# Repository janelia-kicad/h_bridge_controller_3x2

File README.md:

# h_bridge_controller_3x2

Authors:

    Peter Polidoro <polidorop@janelia.hhmi.org>

License:

    BSD

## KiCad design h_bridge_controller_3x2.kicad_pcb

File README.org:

#+TITLE: h_bridge_controller_3x2
#+AUTHOR: Peter Polidoro
#+EMAIL: peter@polidoro.io

* Repository Information
  - Author :: Peter Polidoro
  - License :: Open-Source Hardware

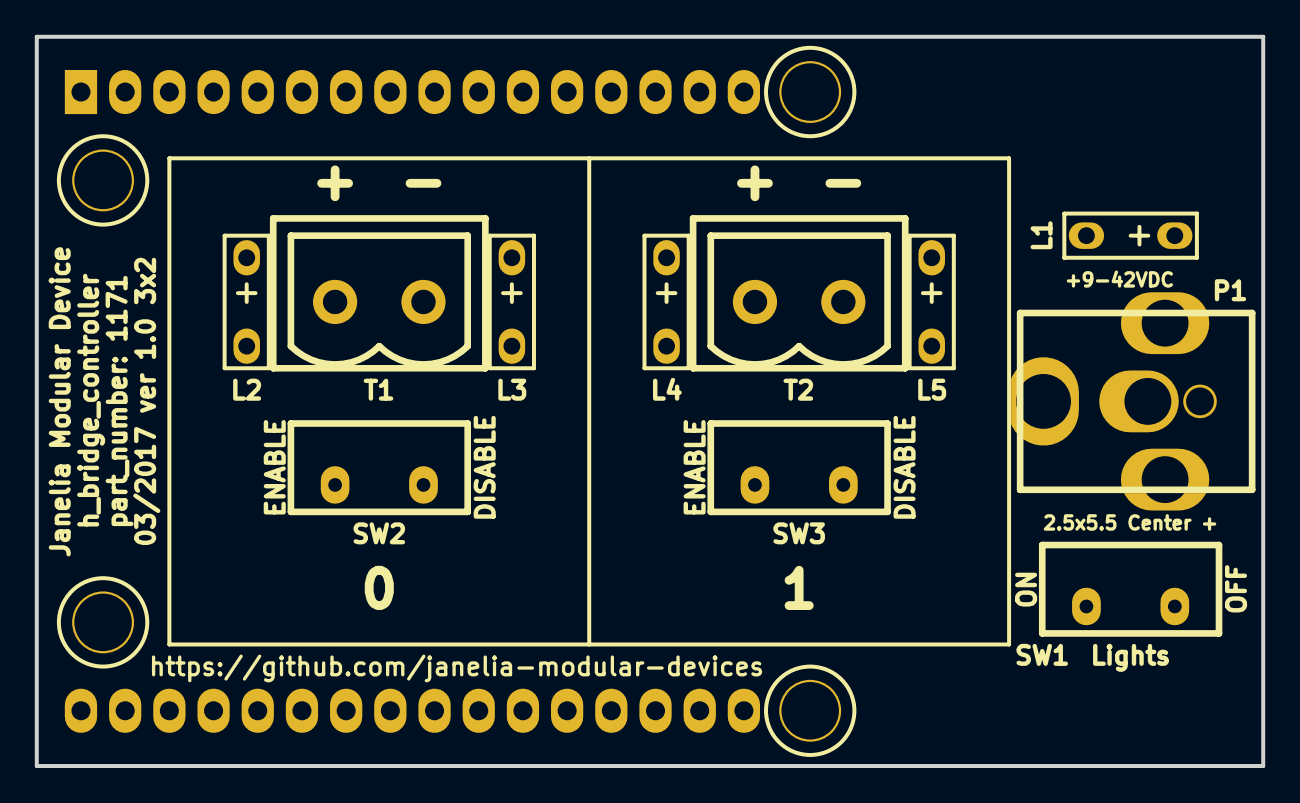
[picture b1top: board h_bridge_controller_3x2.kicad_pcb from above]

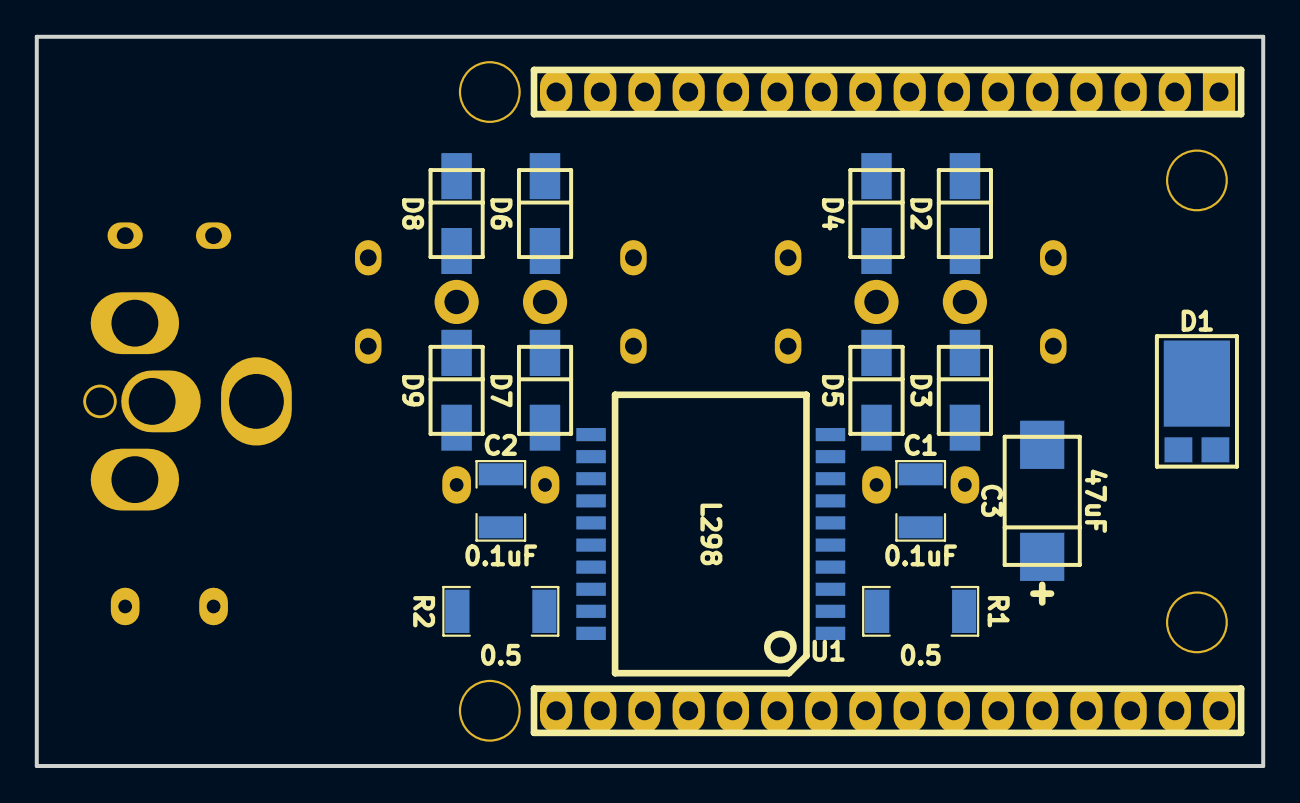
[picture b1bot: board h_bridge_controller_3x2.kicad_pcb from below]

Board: 2 copper layers, 70.5 x 41.9 mm, 27 parts (15 on the bottom side), 19 nets, no tracks yet.

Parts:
C1, C2: 0.1uF; SM1210
C3: 47uF; SM2917_POL
D1: diode_schottky_45V_10A; CFP15
D2, D3, D4, D5, D6, D7, D8, D9: diode_schottky_40V_1A; DO-214AC_SMA
L1, L2, L3, L4, L5: LED_24V; LED_555-3XXX
MDB1: MODULAR_DEVICE_BASE_3X2_MALE
P1: PWR_JACK_2.5x5.5; DCJACK_2PIN_HIGHCURRENT
R1, R2: 0.5; SM2010
SW1, SW2, SW3: SPST_SLIDE_AS
T1, T2: TERM_BLK_HDR_2POS_VERT_0.2IN
U1: L298; POWERSO20

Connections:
/DIR_A_0: MDB1.18, U1.7
/DIR_A_1: MDB1.20, U1.13
/DIR_B_0: MDB1.19, U1.9
/DIR_B_1: MDB1.21, U1.15
/ENABLE_0: MDB1.22, U1.8
/ENABLE_1: MDB1.23, U1.14
/SENSE_0: MDB1.14, R1.1, U1.2
/SENSE_1: MDB1.15, R2.1, U1.19
/USER_ENABLE_0: MDB1.5, SW2.1
/USER_ENABLE_1: MDB1.6, SW3.1
/h_bridge_0/OUT_+_0: D2.2, D3.1, L2.1, T1.1, U1.4
/h_bridge_0/OUT_+_1: D6.2, D7.1, L4.1, T2.1, U1.16
/h_bridge_0/OUT_-_0: D4.2, D5.1, L3.1, T1.2, U1.5
/h_bridge_0/OUT_-_1: D8.2, D9.1, L5.1, T2.2, U1.17
GND: C1.2, C2.2, C3.2, D3.2, D5.2, D7.2, D9.2, MDB1.GND, P1.2, R1.2, R2.2, SW1.1, SW2.3, SW3.3, U1.1, U1.10, U1.11, U1.20
LED_GND: L1.2, L2.2, L3.2, L4.2, L5.2, SW1.3
VAA: C1.1, C3.1, D1.2, D2.1, D4.1, D6.1, D8.1, L1.1, P1.1, U1.6
VDD: D1.1, MDB1.VDD
VEE: C2.1, MDB1.VEE, U1.12

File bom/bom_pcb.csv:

Item,Reference(s),Value,Quantity,Description,PartNumber,Vendor
1,C1 C2,0.1uF,2,CAP CER 0.1UF 50V 10% X7R 1210,399-13229-1-ND,digikey
2,C3,47uF,1,CAP TANT 47UF 35V 10% 2917,399-3821-1-ND,digikey
3,D1,diode_schottky_45V_10A,1,DIODE SCHOTTKY 45V 10A CFP15,568-11697-1-ND,digikey
4,D2 D3 D4 D5 D6 D7 D8 D9,diode_schottky_40V_1A,8,DIODE SCHOTTKY 40V 1A SMA,SS14CT-ND,digikey
5,L1 L2 L3 L4 L5,LED_24V,5,LED 2MM 24V VERTICAL RED PC MNT,350-1723-ND,digikey
6,MDB1,MODULAR_DEVICE_BASE_3X2_MALE,2,16 Position Header Through Hole Male Pins,S1011E-16-ND,digikey
7,P1,PWR_JACK_2.5x5.5,1,CONN PWR JACK DC 2.5X5.5 8A T/H,CP-063BH-ND,digikey
8,R1 R2,0.5,2,RES SMD 0.5 OHM 1% 1W 2010,CSRN2010FKR500CT-ND,digikey
9,SW1 SW2 SW3,SPST_SLIDE_AS,3,SWITCH SLIDE SPST 0.4VA 28V,360-2610-ND,digikey
10,T1 T2,TERM_BLK_HDR_2POS_VERT_0.2IN,2,TERM BLOCK HDR 2POS VERT 5.08MM,277-1150-ND,digikey
11,U1,L298,1,IC BRIDGE DRIVER PAR 20POWERSO,497-3624-1-ND,digikey

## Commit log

2017-01-24 Initial commit.
2017-03-07 Added template_3x2 files.
2017-03-07 Added components and footprints.
2017-03-07 Progress towards v1.0.
2017-03-08 Finished version 1.0.
2017-03-24 Updated documentation.
2017-06-15 Removed .cmp file.
2017-07-14 Moved edges.
2017-09-13 Updated 0.1uF capacitors.
2017-09-22 Removed extra libraries.
2018-01-08 Updated to v4.
2018-01-08 Added v4 files.
2018-01-08 Updated gitignore.
2018-03-09 Update license from software to hardware.
2018-04-12 README.md -> README.org.
2018-04-19 Added .DS_Store to .gitignore.
2018-05-16 Added generate_kicad_documentation submodule.
2018-05-17 Updated submodules.
2018-08-12 Marked extra Teensy pins.
2018-08-12 Removed v4 files.
2018-08-24 Removed F.SilkS from pads.
2018-08-24 Renamed (SMA) to _SMA.
2018-08-27 Removed *.SilkS from pads.
2021-09-16 Update email address
2021-09-21 Remove ignored files
2022-02-22 Add guix files
2022-02-23 Add guix documentation
